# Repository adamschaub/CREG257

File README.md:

CREG257
=======

Phone-Key senior design project.

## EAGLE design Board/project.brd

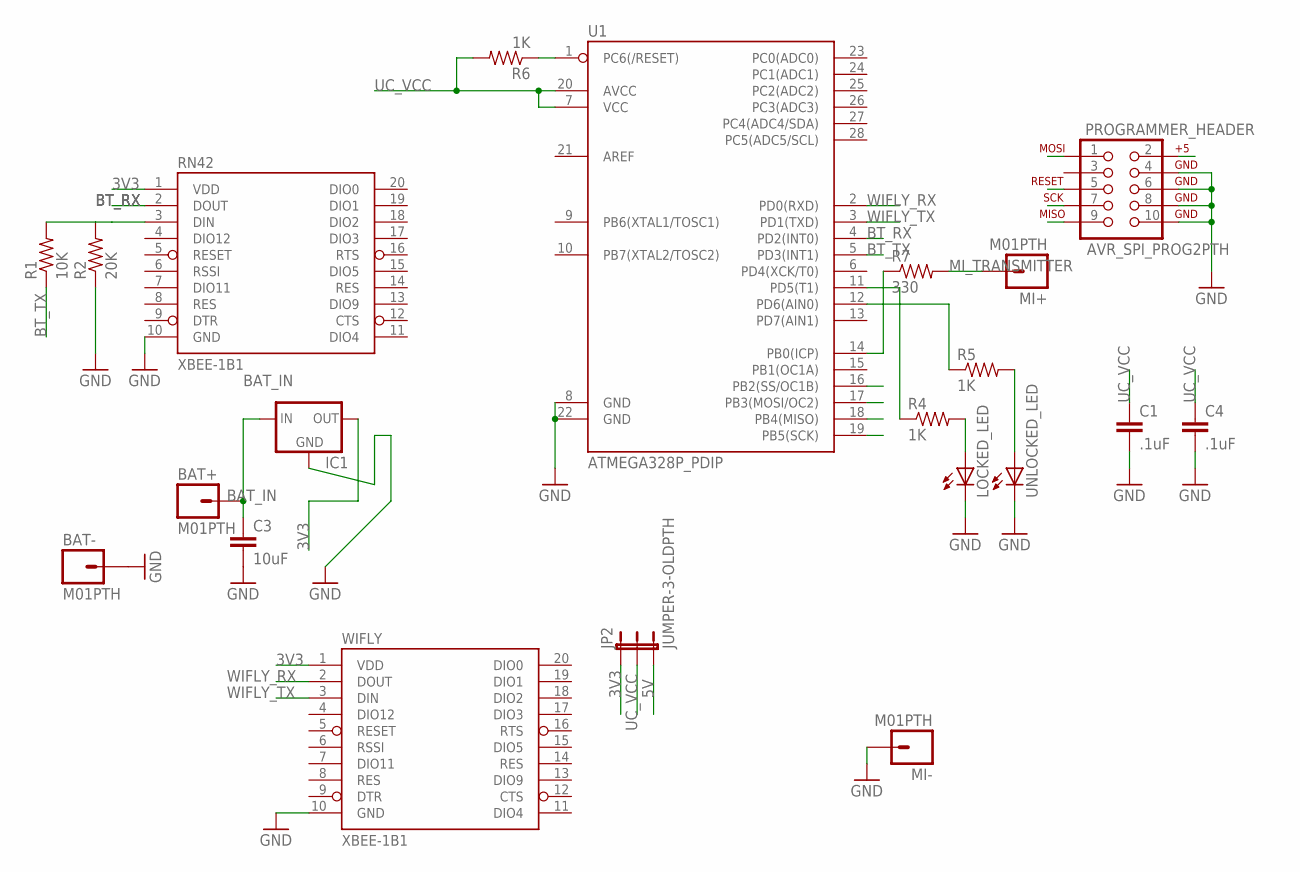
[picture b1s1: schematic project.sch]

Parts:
BAT+: M01PTH; 1X01
BAT-: M01PTH; 1X01
C1, C4: .1uF; CAP-PTH-SMALL
C3: 10uF; CAP-PTH-SMALL
IC1: V_REG_78XXSIDE; 78XXL
JP2: JUMPER-3-OLDPTH; 1X03
LOCKED_LED: LED5MM
MI+: M01PTH; 1X01
MI-: M01PTH; 1X01
PROGRAMMER_HEADER: AVR_SPI_PROG2PTH; AVR_ICSP
R1: 10K; AXIAL-0.3
R2: 20K; AXIAL-0.3
R4, R5, R6: 1K; AXIAL-0.3
R7: 330; AXIAL-0.3
RN42: XBEE-1B1; XBEE-1
U1: ATMEGA328P_PDIP; DIL28-3
UNLOCKED_LED: LED5MM
WIFLY: XBEE-1B1; XBEE-1

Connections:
3V3: IC1.OUT, JP2.1, RN42.1 (VDD), WIFLY.1 (VDD)
5V: JP2.3, PROGRAMMER_HEADER.2
BAT_IN: BAT+.1, C3.1, IC1.IN
BT_RX: RN42.2 (DOUT), U1.4 (PD2(INT0))
BT_TX: R1.P$1 (1), U1.5 (PD3(INT1))
GND: BAT-.1, C1.2, C3.2, C4.2, IC1.GND, LOCKED_LED.K (C), MI-.1, PROGRAMMER_HEADER.4, PROGRAMMER_HEADER.6, PROGRAMMER_HEADER.8, PROGRAMMER_HEADER.10, R2.P$1 (1), RN42.10 (GND), U1.8 (GND), U1.22 (GND), UNLOCKED_LED.K (C), WIFLY.10 (GND)
MISO: PROGRAMMER_HEADER.9, U1.18 (PB4(MISO))
MI_TRANSMITTER: MI+.1, R7.P$2 (2)
MOSI: PROGRAMMER_HEADER.1, U1.17 (PB3(MOSI/OC2))
unnamed: R1.P$2 (2), R2.P$2 (2), RN42.3 (DIN)
unnamed: R5.P$1 (1), U1.12 (PD6(AIN0))
unnamed: R4.P$1 (1), U1.11 (PD5(T1))
unnamed: LOCKED_LED.A, R4.P$2 (2)
unnamed: R5.P$2 (2), UNLOCKED_LED.A
unnamed: R7.P$1 (1), U1.14 (PB0(ICP))
RESET: PROGRAMMER_HEADER.5, R6.P$1 (1), U1.1 (PC6(/RESET))
SCK: PROGRAMMER_HEADER.7, U1.19 (PB5(SCK))
UC_VCC: C1.1, C4.1, JP2.2, R6.P$2 (2), U1.7 (VCC), U1.20 (AVCC)
WIFLY_RX: U1.2 (PD0(RXD)), WIFLY.2 (DOUT)
WIFLY_TX: U1.3 (PD1(TXD)), WIFLY.3 (DIN)

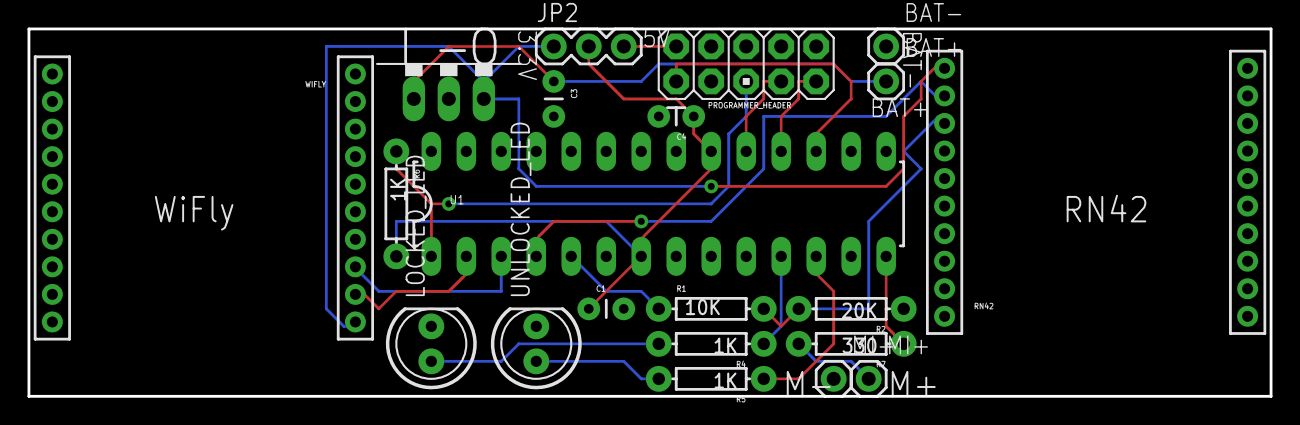
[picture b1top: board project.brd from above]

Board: 2 copper layers, 90.2 x 26.7 mm, 21 parts (0 on the bottom side), 20 nets.

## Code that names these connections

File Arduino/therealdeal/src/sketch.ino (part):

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
#define KEY_SIZE (256/8)	// int is (I believe) 8 bits, so use byte size instead of bit size

#define LOCKED_PIN 		5	// PB4
#define UNLOCKED_PIN	6	// PB1

#define	LOCK_INIT		0
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#define CHECK_UNLOCKED	10	// LOW if true - PB2 - GREEN
//#define MOTOR_READING	5	// analog input for reading motor current draw

#define MI_OUT_PIN		8	// PB0
#define	TRANSMIT_FREQ	101	// sampling freq of phone, in hertz
#define PERIOD (1000000/TRANSMIT_FREQ)	// period, in us

#define BT_RX		   	2
#define BT_TX		   	3
#define BT_CMDBUF_LEN   200
#define MAC_ADDR_SIZE	12

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#define CONNECTING	1
#define CONNECTED	2

#define WIFLY_RX	0	// WHITE ON TOP, GREEN ON BOTTOM
#define WIFLY_TX	1

#define CMD_LOCK	0
#define CMD_UNLOCK	1
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
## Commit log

2013-10-06 Initial Android project commit.
2013-10-06 Initial commit of Arduino stuff.
2013-10-24 Adds AES library for Arduino, AES stuff for Android, other debugging stuff.
2013-11-07 added bluetooth code for arduino
2013-11-07 Initial commit of Bluetooth stuff.
2013-11-08 Reading/writing seems to be working
2013-11-14 Sending/receiving works ok, encryption untested...
2013-11-16 Arduino program for receiving data, decrypting it, and turning LED on if it matches passcode
2013-11-16 Adds encryption.
2013-11-16 Init seems to be working?
2013-11-17 Adds lock/unlock buttons to app.
2013-11-17 Removed Go button, added persistant storage on Arduino for keys and passcodes
2013-11-20 Removes some debugging printing
2013-11-20 Start of key sharing stuff.
    Adds button, which creates a file and launches a "Send email" intent
    which prompts the user to send an email with the created file attached.
    To send the file, because it's in internal storage, had to create a ContentProvider
    so the email app can access it.
    Also adds an intent-filter to the manifest so when you select a *.phnky attachment,
    our app is listed as one of the "Complete this action with" apps. Tested for Gmail
2013-11-20 This should actually work now after just the first init...
2013-11-20 Adds persistant key/pass/lockid storage.
    KeyPassFileOpener is called to open .phnky email attachments. It uses
    FileManager to add the info to our internal file structure.
    Our internal file structure is just a directory ("lockfiles") under
    our app's internal directory (Context.getFilesDir()). Each lock is stored
    in a new file, starting with 1.phnky and counting up. The file format is:
    32 byte key, 1 byte passcode length, passcode length, 1 byte lock ID, lock ID.
2013-11-25 Adds motor spinning stuff. UNTESTED\!
2013-12-01 Adds MI challenge to authentication procedure
2013-12-01 Should check response (ACK/NAK) from Arduino now
2013-12-01 MI challenge kinda sorta working
2013-12-01 Seems to be working?
2013-12-16 Forgot to add this file...
2013-12-16 Switch voltage ref source
2013-12-23 Testing...
2014-01-02 Utility program for configuring BT module.
2014-01-09 Beginning of moving everything into a service.
2014-01-10 Adds MI listener to service
2014-01-15 Lots of refactoring. Still need to get encryption working.
2014-01-15 Encryption works now...
2014-01-17 Better handling of BT state.
2014-01-17 Refactoring and slight change to authentication sequence.
    Refactors the authentication sequence so each step is in a seperate
    function. This cleans up the main loop and means we can remove the gotos.
    The command (unlock or lock) is now sent from the phone as soon as the BT module
    connects. This way, as soon as the door receives a good MI challenge response,
    it can execute the command without any more communications with the phone.
2014-01-19 Cleaned up a bit.
2014-01-20 Preparing for multidevice config.
2014-01-22 Implements ACL on Arduino.
    ACL is stored persistently in EEPROM. Currently each entry consists
    of just a key and MAC address, and is only 44 bytes. Since the Atmega328
    has 1024 bytes of EEPROM, there's no need to use an external chip.
2014-01-22 Removes passcode, replaces KeyPassData list with HashMap for key, MAC address.
2014-01-22 Adds onDestroy() for service.
2014-01-24 First time initialization should work maybe.
2014-01-25 Web server request stuff.
2014-01-26 Maybe directly setting the pin improves timing issues?
2014-01-27 Some basic error correction for shifted MI transmissions.
2014-02-11 Lots of website backbone. Registratoin/Authentication working
2014-02-17 Initial commit for schematic.
2014-02-17 Added pads for MI transmitter and battery power, plus PCB layout.
2014-02-17 Changed some pins for better routing, passes DRC now.
2014-02-17 Updates for running it off an Arduino.
2014-02-18 Working on heroku compatibility
2014-02-18 Package.json updates
2014-02-18 Trying to get Heroku to recognize node
2014-02-18 More package.json changes
2014-02-18 initialized local repo
2014-02-18 Added wifly serial code
2014-02-18 Messed up git levels a bit when doping around with server.
2014-02-18 A little more clean up. Everything should be in the right folder now.
2014-02-19 Changes some pins for better board layout.
2014-02-19 Better board layout, everything that needs to be should be connected, passes DRC.
2014-02-19 Layout actually works, added silkscreen.
2014-02-19 Updated board.
2014-02-21 Layout of first board submitted to be build.
2014-03-02 Restore server progress
2014-03-03 Starts interfacing app with website.
2014-03-03 Changes style of buttons.
2014-03-11 Updates to send MAC address.
2014-03-11 Adds activity to go to after loggin in.
2014-03-12 Separated website and tcp files
2014-03-15 Adds basic Wifly support, tunes timing for MI transmitter.
2014-03-18 updated mobile routes, contact and eKey schemas implemented
2014-03-18 Changed db config to connect to localhost of main cannot be reached
2014-03-18 Removed tcp submodule, updated db config to connect to localhost when it cannot reach the remote db
2014-03-19 Some tweaks.
2014-03-19 Adds stuff for managing your lock from the app.
2014-03-21 Adds another error correction scheme.
2014-03-21 Copy corrected data to correct array...
2014-03-23 Adds wifly-server communication.
2014-03-24 Redo the account page layout.
2014-03-24 Some fixes.
2014-03-25 TCP server update
2014-03-25 Added id request timeout
2014-03-25 Some stuff.
2014-03-26 MAC addresses passed without colons
2014-03-26 Adds stupid hack.
2014-03-26 Tries to not die on disconnect.
2014-03-26 More stuff.
2014-03-26 Adds another error correction method.
2014-04-05 Updates lock in DB when status update from lock received.
2014-04-06 Some changes to app to use local site instead of web.
2014-04-06 Changes to TCP server for updating lock status.
2014-04-11 Some updates to Arduino sketck, motor turns now on lock/unlock.
2014-04-15 updates to the tcp server

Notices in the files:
parts and their libraries:
SparkFun-DigitalIC: Licensing: Creative Commons ShareAlike 4.0 International - https://creativecommons.org/licenses/by-sa/4.0
